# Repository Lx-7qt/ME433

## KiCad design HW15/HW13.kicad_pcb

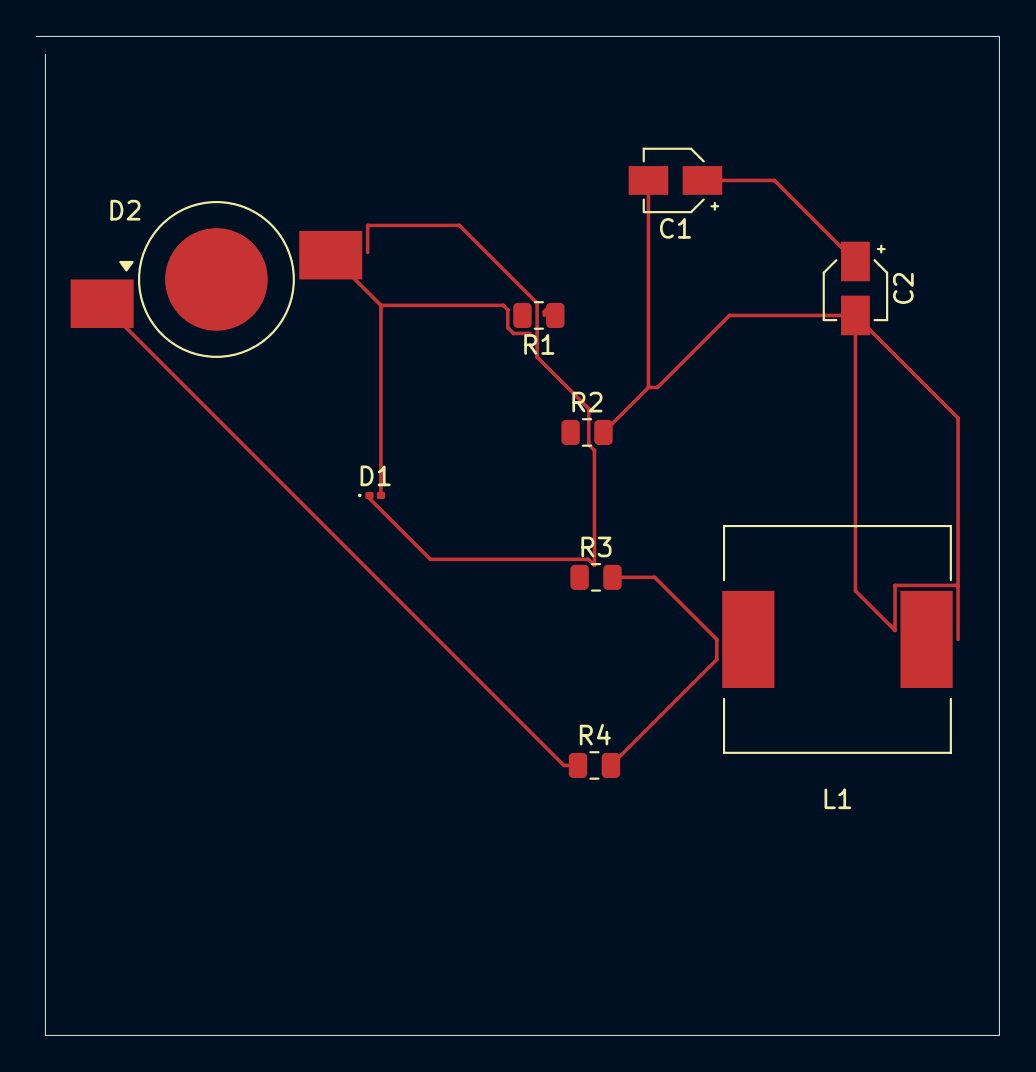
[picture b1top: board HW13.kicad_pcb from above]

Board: 2 copper layers, 53.5 x 55.5 mm, 9 parts (0 on the bottom side), 6 nets.

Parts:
C1, C2: 22 uF; CP_Elec_3x5.3
D1: D_Schottky; D_0201_0603Metric
D2: Red; LED_1W_3W_R8
L1: 4.7 uH; L_12x12mm_H4.5mm
R1: 110k; R_0805_2012Metric
R2: 15k; R_0805_2012Metric
R3: 20k; R_0805_2012Metric
R4: 1k; R_0805_2012Metric

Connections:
+5V: D1.2 (K), D2.2 (A), R1.1
GND: C1.2, C2.2, R2.2, R3.2, R4.2
unnamed: D1.1 (A), L1.2
unnamed: D2.1 (K), R4.1
unnamed: R1.2, R2.1
VCC: C1.1, C2.1, L1.1

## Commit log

2025-05-29 update HW2
2025-05-31 update HW3
2025-05-31 update HW6
2025-06-01 update HW7
2025-06-01 update HW9
2025-06-01 update HW10
2025-06-02 update HW11
2025-06-03 update HW13
2025-06-03 update HW15
2025-06-03 update HW5
2025-06-04 update HW8
2025-06-05 update HW16
2025-06-05 update HW4
2025-06-05 update HW12
